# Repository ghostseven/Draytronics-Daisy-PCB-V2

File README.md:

# Draytronics-Daisy-PCB-V2

An open source macro pad with a rotary encoder and OLED panel, this is an alternative version to the original through hole Daisy kit. More info / PCB designs available at [draytronics.co.uk/daisyV2](https://www.draytronics.co.uk/daisyv2/)

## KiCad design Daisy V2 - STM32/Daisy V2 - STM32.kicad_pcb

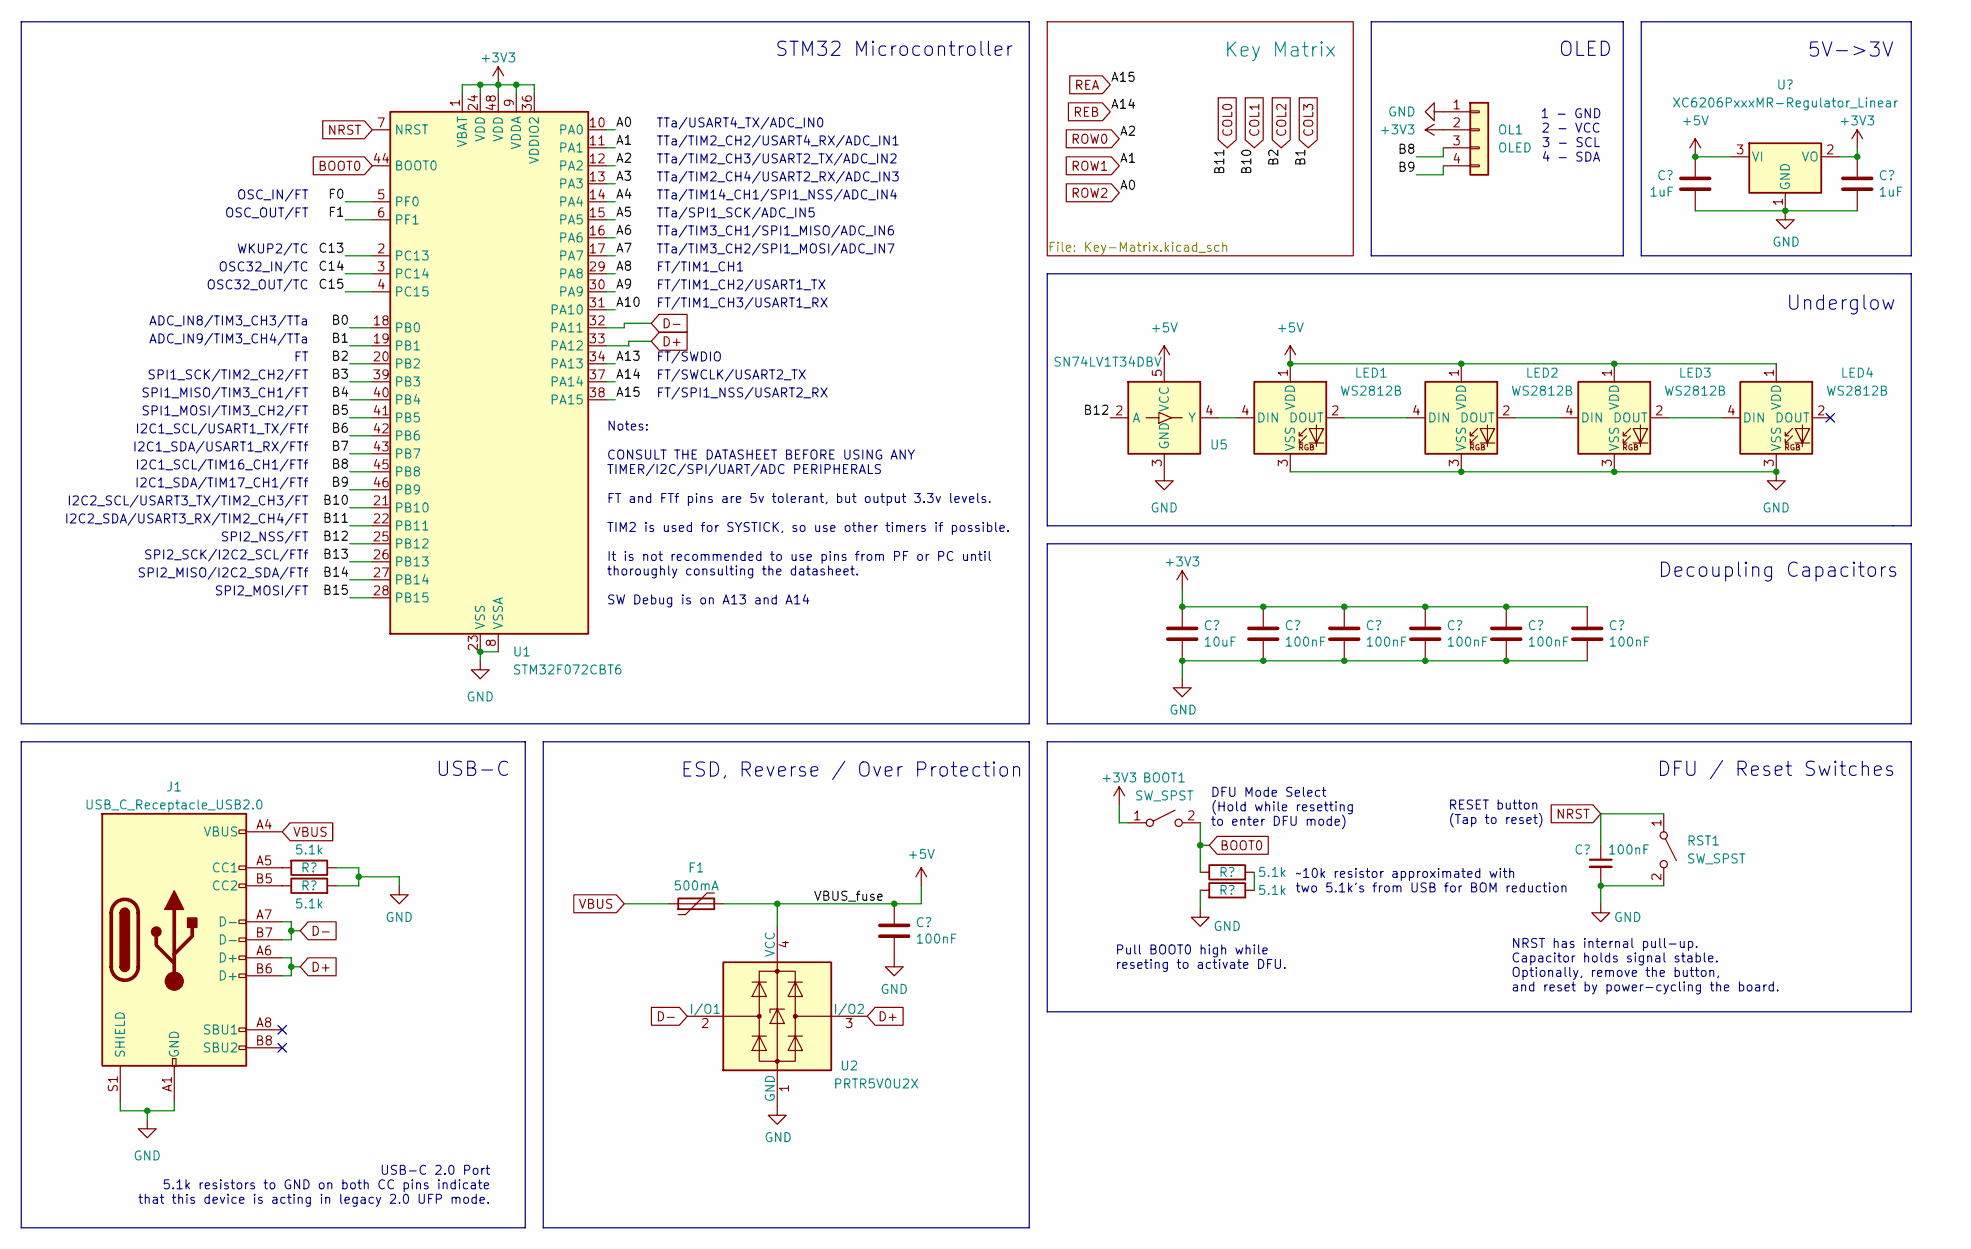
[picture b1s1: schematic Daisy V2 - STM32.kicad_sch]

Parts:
BOOT1: SW_SPST; SW_SPST_TL3342; LCSC Part # C2886897
C1, C3, C4, C5, C6, C7, C8: 100nF; C_0402_1005Metric; LCSC Part # C307331
C2: 10uF; C_0603_1608Metric; LCSC Part # C19702
C9, C10: 1uF; C_0402_1005Metric; LCSC Part # C52923
F1: 500mA; Fuse_1206_3216Metric; LCSC Part # C135341
J1: USB_C_Receptacle_USB2.0; USB_C_Receptacle_HRO_TYPE-C-31-M-12; JlcRotOffset 180
LED1, LED2, LED3, LED4: WS2812B; LED_WS2812B_PLCC4_5.0x5.0mm_P3.2mm; LCSC Part # C2843785
OL1: OLED; SSD1306-0.91-OLED-4pin-128x32
R1, R2, R3, R4: 5.1k; R_0402_1005Metric; LCSC Part # C105872
RST1: SW_SPST; SW_SPST_TL3342; LCSC Part # C2886897
U1: STM32F072CBT6; LQFP-48_7x7mm_P0.5mm; JlcRotOffset 90
U2: PRTR5V0U2X; SOT-143; LCSC Part # C2827688
U3: XC6206PxxxMR-Regulator_Linear; SOT-23; LCSC Part # C5446
U5: SN74LV1T34DBV; SOT-23-5; MPN SN74LV1T34DBVR; LCSC Part # C100024

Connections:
+3V3: BOOT1.1 (A), C2.1, C3.1, C4.1, C5.1, C6.1, C7.1, C10.1, OL1.2, U1.1 (VBAT), U1.9 (VDDA), U1.24 (VDD), U1.36 (VDDIO2), U1.48 (VDD), U3.2 (VO); also elsewhere on the board
+5V: C8.1, C9.1, F1.2, LED1.1 (VDD), LED2.1 (VDD), LED3.1 (VDD), LED4.1 (VDD), U2.4 (VCC), U3.3 (VI), U5.5 (VCC)
/A3: U1.13 (PA3)
/A4: U1.14 (PA4)
/A5: U1.15 (PA5)
/A6: U1.16 (PA6)
/A7: U1.17 (PA7)
/A8: U1.29 (PA8)
/A9: U1.30 (PA9)
/A10: U1.31 (PA10)
/A13: U1.34 (PA13)
/B0: U1.18 (PB0)
/B3: U1.39 (PB3)
/B4: U1.40 (PB4)
/B5: U1.41 (PB5)
/B6: U1.42 (PB6)
/B7: U1.43 (PB7)
/B8: OL1.3, U1.45 (PB8)
/B9: OL1.4, U1.46 (PB9)
/B12: U1.25 (PB12), U5.2 (A)
/B13: U1.26 (PB13)
/B14: U1.27 (PB14)
/B15: U1.28 (PB15)
/C13: U1.2 (PC13)
/C14: U1.3 (PC14)
/C15: U1.4 (PC15)
/F0: U1.5 (PF0)
/F1: U1.6 (PF1)
BOOT0: BOOT1.2 (B), R3.1, U1.44 (BOOT0)
COL0: U1.22 (PB11); also elsewhere on the board
COL1: U1.21 (PB10); also elsewhere on the board
COL2: U1.20 (PB2); also elsewhere on the board
COL3: U1.19 (PB1); also elsewhere on the board
D+: J1.A6 (D+), J1.B6 (D+), U1.33 (PA12), U2.3 (I/O2)
D-: J1.A7 (D-), J1.B7 (D-), U1.32 (PA11), U2.2 (I/O1)
GND: C1.2, C2.2, C3.2, C4.2, C5.2, C6.2, C7.2, C8.2, C9.2, C10.2, J1.A1 (GND), J1.A12 (GND), J1.B1 (GND), J1.B12 (GND), J1.S1 (SHIELD), LED1.3 (VSS), LED2.3 (VSS), LED3.3 (VSS), LED4.3 (VSS), OL1.1, R1.1, R2.2, R4.2, RST1.2 (B), U1.8 (VSSA), U1.23 (VSS), U1.35 (VSS), U1.47 (VSS), U2.1 (GND), U3.1 (GND), U5.3 (GND); also elsewhere on the board
NRST: C1.1, RST1.1 (A), U1.7 (NRST)
unnamed: J1.A5 (CC1), R1.2
unnamed: J1.B5 (CC2), R2.1
unnamed: LED1.4 (DIN), U5.4 (Y)
unnamed: LED1.2 (DOUT), LED2.4 (DIN)
unnamed: LED2.2 (DOUT), LED3.4 (DIN)
unnamed: LED3.2 (DOUT), LED4.4 (DIN)
unnamed: R3.2, R4.1
REA: U1.38 (PA15); also elsewhere on the board
REB: U1.37 (PA14); also elsewhere on the board
ROW0: U1.12 (PA2); also elsewhere on the board
ROW1: U1.11 (PA1); also elsewhere on the board
ROW2: U1.10 (PA0); also elsewhere on the board
VBUS: F1.1, J1.A4 (VBUS), J1.A9 (VBUS), J1.B4 (VBUS), J1.B9 (VBUS)

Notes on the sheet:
SPI1_SCK/TIM2_CH2/FT
STM32 Microcontroller
FT/TIM1_CH1
FT/TIM1_CH3/USART1_RX
SPI2_NSS/FT
Notes: CONSULT THE DATASHEET BEFORE USING ANY TIMER/I2C/SPI/UART/ADC PERIPHERALS FT and FTf pins are 5v tolerant, but output 3.3v levels. TIM2 is used for SYSTICK, so use other timers if possible. It is not recommended to use pins from PF or PC until thoroughly consulting the datasheet. SW Debug is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
TTa/TIM2_CH4/USART2_RX/ADC_IN3
NRST has internal pull-up. Capacitor holds signal stable. Optionally, remove the button, and reset by power-cycling the board.
FT/SWDIO
Decoupling Capacitors
SPI1_MOSI/TIM3_CH2/FT
ADC_IN9/TIM3_CH4/TTa
I2C2_SCL/USART3_TX/TIM2_CH3/FT
DFU / Reset Switches
SPI2_MISO/I2C2_SDA/FTf
FT/SWCLK/USART2_TX
I2C1_SCL/TIM16_CH1/FTf
Underglow
~10k resistor approximated with two 5.1k's from USB for BOM reduction
TTa/TIM2_CH2/USART4_RX/ADC_IN1
USB-C 2.0 Port 5.1k resistors to GND on both CC pins indicate that this device is acting in legacy 2.0 UFP mode.
TTa/TIM2_CH3/USART2_TX/ADC_IN2
OSC_IN/FT
DFU Mode Select (Hold while resetting to enter DFU mode)
WKUP2/TC
I2C2_SDA/USART3_RX/TIM2_CH4/FT
ADC_IN8/TIM3_CH3/TTa
1 - GND 2 - VCC 3 - SCL 4 - SDA
RESET button (Tap to reset)
Pull BOOT0 high while reseting to activate DFU.
I2C1_SDA/TIM17_CH1/FTf
USB-C
TTa/SPI1_SCK/ADC_IN5
TTa/TIM3_CH1/SPI1_MISO/ADC_IN6
TTa/TIM3_CH2/SPI1_MOSI/ADC_IN7
OSC32_OUT/TC
FT/SPI1_NSS/USART2_RX
SPI1_MISO/TIM3_CH1/FT
OSC32_IN/TC
OLED

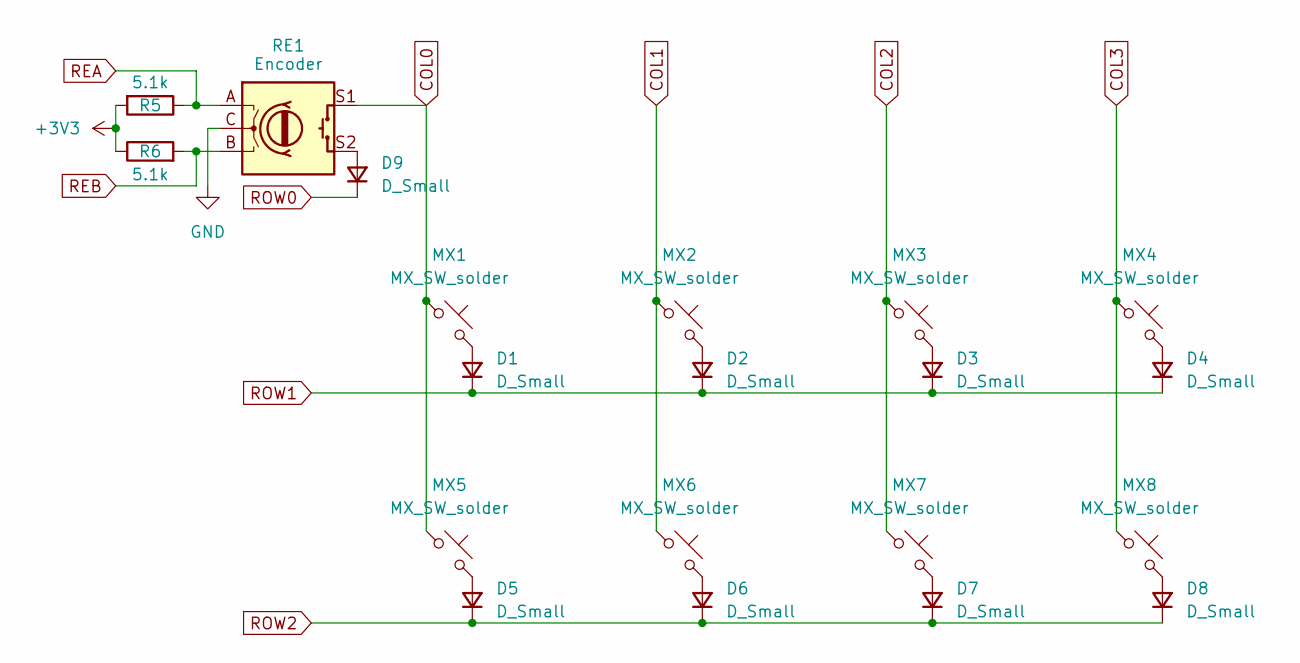
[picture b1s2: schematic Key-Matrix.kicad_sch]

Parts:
D1, D2, D3, D4, D5, D6, D7, D8, D9: D_Small; D_SOD-123; LCSC Part # C81598
MX1, MX2, MX3, MX4, MX5, MX6, MX7, MX8: MX_SW_solder; SW_MX_1u
R5, R6: 5.1k; R_0402_1005Metric; LCSC Part # C105872
RE1: Encoder; RotaryEncoder_Alps_EC11E-Switch_Vertical_H20mm

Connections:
+3V3: R5.2, R6.1; also elsewhere on the board
COL0: MX1.1, MX5.1, RE1.S1; also elsewhere on the board
COL1: MX2.1, MX6.1; also elsewhere on the board
COL2: MX3.1, MX7.1; also elsewhere on the board
COL3: MX4.1, MX8.1; also elsewhere on the board
GND: RE1.C; also elsewhere on the board
unnamed: D1.2 (A), MX1.2
unnamed: D2.2 (A), MX2.2
unnamed: D3.2 (A), MX3.2
unnamed: D4.2 (A), MX4.2
unnamed: D5.2 (A), MX5.2
unnamed: D6.2 (A), MX6.2
unnamed: D7.2 (A), MX7.2
unnamed: D8.2 (A), MX8.2
unnamed: D9.2 (A), RE1.S2
REA: R5.1, RE1.A; also elsewhere on the board
REB: R6.2, RE1.B; also elsewhere on the board
ROW0: D9.1 (K); also elsewhere on the board
ROW1: D1.1 (K), D2.1 (K), D3.1 (K), D4.1 (K); also elsewhere on the board
ROW2: D5.1 (K), D6.1 (K), D7.1 (K), D8.1 (K); also elsewhere on the board

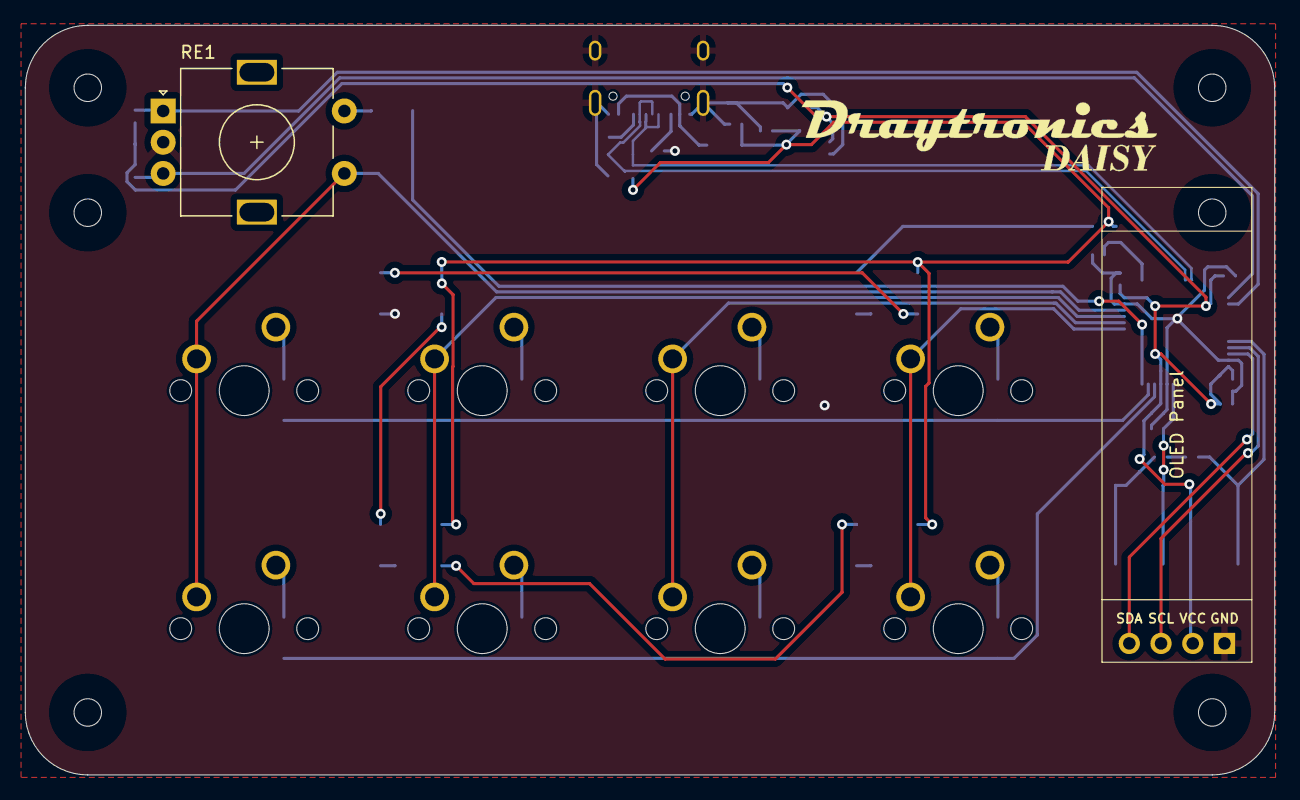
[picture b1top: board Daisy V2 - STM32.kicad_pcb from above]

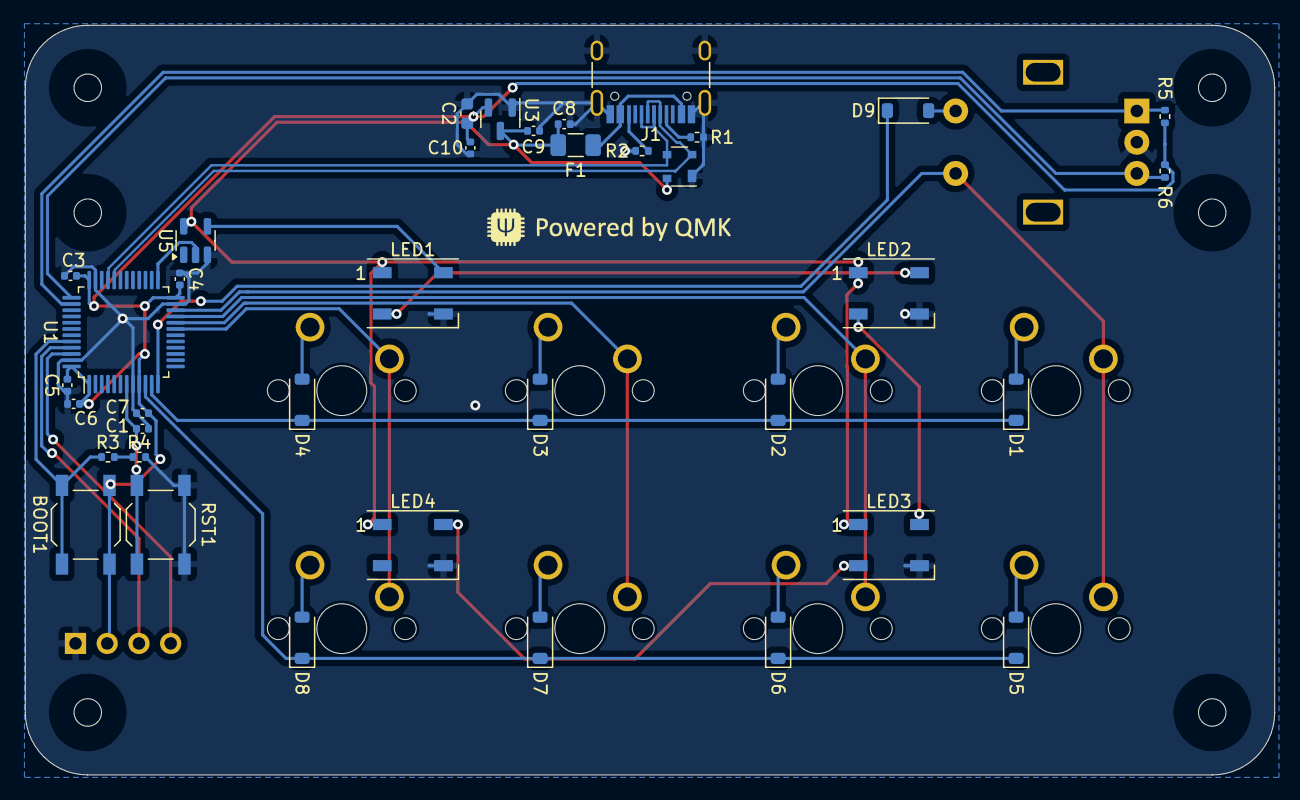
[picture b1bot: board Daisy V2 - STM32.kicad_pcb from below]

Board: 2 copper layers, 100.0 x 60.0 mm, 47 parts (37 on the bottom side), 36 nets.

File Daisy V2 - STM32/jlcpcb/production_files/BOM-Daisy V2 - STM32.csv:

Comment,Designator,Footprint,LCSC
SN74LV1T34DBV,U5,SOT-23-5,C100024
5.1k,"R1,R2,R3,R4,R5,R6",R_0402_1005Metric,C105872
500mA,F1,Fuse_1206_3216Metric,C135341
10uF,C2,C_0603_1608Metric,C19702
PRTR5V0U2X,U2,SOT-143,C2827688
SW_SPST,"BOOT1,RST1",SW_SPST_TL3342,C2886897
USB_C_Receptacle_USB2.0,J1,USB_C_Receptacle_HRO_TYPE-C-31-M-12,C2988369
100nF,"C1,C3,C4,C5,C6,C7,C8",C_0402_1005Metric,C307331
1uF,"C10,C9",C_0402_1005Metric,C52923
XC6206PxxxMR-Regulator_Linear,U3,SOT-23,C5446
D_Small,"D1,D2,D3,D4,D5,D6,D7,D8,D9",D_SOD-123,C81598
STM32F072CBT6,U1,LQFP-48_7x7mm_P0.5mm,C81720
MX_SW_solder,MX4,SW_MX_1u,
MX_SW_solder,MX8,SW_MX_1u,
MX_SW_solder,MX7,SW_MX_1u,
MX_SW_solder,MX3,SW_MX_1u,
MX_SW_solder,MX6,SW_MX_1u,
MX_SW_solder,MX1,SW_MX_1u,
MX_SW_solder,MX2,SW_MX_1u,
MX_SW_solder,MX5,SW_MX_1u,

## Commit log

2024-06-06 README.md changes and removing .DS_Store junk.
2024-06-06 README.md Update
